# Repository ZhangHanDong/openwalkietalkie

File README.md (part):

# Cohdl OpenWalkieTalkie

[Website and downloads](https://openwalkietalkie.org/) ·
[Latest release](https://github.com/conol-ai/openwalkietalkie/releases/latest)

Firmware and [routed BodyV5 r3 hardware design](hardware/rev-a/README.md) for
OpenWalkieTalkie, a handheld with a touch screen, a scroll wheel, PTT, Enter,
Esc, Shift and two front macro keys. The custom hardware includes a four-layer main PCB and
two-layer encoder PCB, with matching fabrication files and populated 3D models.

The firmware turns the device into the **Agent Command Deck**: a handheld
status board and radio for someone running several AI agent sessions at once.
The screen shows who needs you, PTT talks to the active agent, and the buttons
answer questions and switch channels.

The Rust / [embassy](https://embassy.dev) firmware currently runs on a **LilyGo
T-Display SF32** development board, which carries a SiFli **SF32LB52x** (Cortex-M33,
16MB NOR, 8MB PSRAM) and the same class of 2.16" CO5300 AMOLED with CST9220
touch. The dev board has no scroll wheel, so the **T-SF32-Keyboard** expansion
stands in for the wheel and buttons.

Sibling to [`openmicrokbd`](https://github.com/conol-ai/openmicrokbd) (v1,
STM32F072) — same approach, different silicon.

## What works today

Boot, the debug UART, the shared I2C bus, keypad and touchscreen input,
battery charging, and the Agent Command Deck's 480x480 UI on the AMOLED:
five faces, the face manager, notifications, the PTT LISTENING overlay and a
built-in demo host. Everything above the drivers is covered by host tests and
rendered previews; **none of the deck has been validated on hardware yet**
(see the [first-flash checklist](docs/deck-device-checklist.md)).

The deck is its own USB/BLE HID device: **Cohdl OpenWalkieTalkie**, VID
`0x1209` PID `0x5754`, one vendor collection (usage page `0xFF00`, report id
6, 64-byte reports). Report channel 2 carries a small system RPC
(`sys.version`, `sys.reboot`, `device.status`); the deck faces talk to a deck
host over channel 5 of the same connection ([deck protocol](#the-deck-host)).

The `1209:5754` allocation has been requested in
[pid.codes PR #1312](https://github.com/pidcodes/pidcodes.github.com/pull/1312)
and is pending registry approval. Application firmware and USB recovery use
the same product ID.

Pair **OpenWalkieTalkie** in macOS Bluetooth settings. The latest computer's bond
key and HID/battery notification preferences are stored in an append-only
flash journal at `0x12710000..0x1271FFFF`, reserved from the application
linker region. Automatic encrypted reconnection after a firmware update has
been verified. Upgrading from firmware that kept keys only in RAM requires
forgetting the old device and pairing once to create the persistent bond.

The journal checks each record's version and CRC, skips torn writes, and
verifies writes by reading them back. It supports 1024 changed records and
never erases flash; an exhausted journal reports a storage error. Unchanged
keys/preferences do not consume records. `tools/flash.sh` writes ELF load
segments and preserves the reserved journal. A whole-chip erase does not.
The Embassy target carries controls, deck traffic and battery status over HID.
On Rev A it also carries the microphone and speaker, as its own BLE GATT
service on the same link rather than as a Bluetooth audio device: a PTT press
streams 16 kHz IMA ADPCM to the host, and the host's spoken replies come back
the same way (`docs/deck-protocol.md`, "Voice"). Over the USB cable the same
frames ride report channel 7 of the HID collection, so a deck on the cable
alone has its voice too, with no pairing; `deckd` uses the cable whenever it
is there and Bluetooth otherwise. The
[native audio target](native/README.md) instead presents the display board's
microphone and speaker as Bluetooth Classic audio (HFP/A2DP) alongside the
same UI.
Both targets show the website's pixel-radio icon and stacked OpenWalkieTalkie
title on a black boot splash, with a small COHDL mark and “A COHDL PROJECT”
credit. After 1.2 seconds, the Agents face appears.
The same radio appears in Settings → About and in the Mac app, Dock, menu bar
and updater. Regenerate the desktop assets with `python3 tools/generate-branding.py`
(Pillow); normal builds use the checked-in images.

Embassy boot log, abridged:

```
SFBL
openwalkietalkie-fw 0.1.0
board: LilyGo T-Display SF32 (dev)
board: holding power rail (PA41)
board: bringing up I2C1 (SCL PA38 / SDA PA37) at 400000 Hz
display: CO5300 initialised (480x480, rotation=0deg)
board: display ready
board: ready
boot: OpenWalkieTalkie splash ready
boot: I2C1 before keyboard power-up:
  0x22 XL9555 GPIO expander (keyboard board)
  0x25 AW21009 keypad LED driver (keyboard board)
  0x34 TCA8418 keypad scanner (keyboard board)
app: Agent Command Deck ready
keypad: TCA8418 ready (5x4 matrix), PA11 interrupt + 50ms fallback
```

## Faces

The screen is a strip of faces, one on screen at a time. The default strip,
left to right: **Agents** (the agent-session roster, home), **Omarchy** (a
remote for the Omarchy/Hyprland desktop), **Macropad**, **Usage**, **System**, **Arcade** and
**Settings**.

- **Boot and home are the Agents face.** Until a deck host says hello the deck
  is empty and every face's header tag reads `offline`; a lost host leaves its
  data on screen, gray, tagged `offline`. Settings → Host → Demo data (off by
  default) fills the deck with built-in demo data instead, tagged `demo`, until
  the first real `hello` clears it.
- **SHIFT+SCROLL moves between faces**, one face per detent, clockwise to the
  right, with hard ends and no wrap. On the dev keypad: hold HOME and press ▼
  or ▲.
- **CANCEL at a face's top level goes home.**
- **Double-SHIFT** (two quick taps of HOME, nothing else in between) opens the
  face manager: reorder, add and remove faces (at most eight, three Macropads).
  Agents and Settings stay pinned.
- **PTT talks to an agent from work faces**, over a full-screen LISTENING
  overlay. On Arcade it is a local game button and never opens the microphone.
- **A new question or finished task raises a toast** for 4 seconds; tapping it
  jumps to the card. Unread notices wait in a drawer (swipe down from the top
  edge), flagged by a pill at the top of the screen, red while a question waits.
- **Idle-home:** after 120 seconds without local input the deck returns to the
  Agents roster (Settings → Display; off, 30, 60 or 120 seconds). It waits for
  a PTT session to end.
- **Sleep locks every local control, including PTT.** Any button, wheel detent
  or touch lights the lock screen. Turn the wheel counterclockwise four ticks
  to unlock; clockwise rotation resets progress. The unlocking ticks and any
  press or touch begun while locked never trigger the underlying screen.

[The Agent Command Deck](docs/agent-command-deck.md) is the full grammar: views,
cards, the manager, notifications, settings and the PTT session rules.

### Fonts

Deck text is Noto Sans (SIL Open Font License, `assets/fonts/`), rasterized
ahead of time into 4-bit glyph atlases by `tools/generate-ui-fonts.py`; the
firmware carries no font engine. The panel is small and dense (480 px over
38.8 mm, about 12 px/mm), so the type ramp runs about 1.6x the mockups' sizes:
15 px for hints, 18 px for tags and labels, 22 px body text, 25 px list rows and
up to 48 px for the big numbers (`RAMP` in `tools/generate-ui-fonts.py` and
`src/ui/theme.rs`). The mockups' layout rectangles are kept where the larger
text fits, and moved where it does not (the question card's choices start
lower; the PTT pill is wider). `tools/generate-ui-fonts.py --check`
regenerates into a temporary directory and diffs; the atlases depend on the
local FreeType build, so a check on another machine may differ.

Chinese text falls back to Noto Sans CJK SC: 28,491 glyphs covering simplified
and traditional Chinese, Extension A, Chinese punctuation and fullwidth
forms. A shared 26 px, 2-bit atlas is filtered to each text size, keeping the
firmware inside the board's application partition. The host uses the same
metrics when wrapping messages. Regenerate it with
`python3 tools/generate-cjk-font.py` (or verify with `--check`); source,
license and coverage details are in `assets/fonts/gen/README.md`.

### The deck host

The deck faces are drawn from data a host daemon pushes over HID channel 5:
agents, cards, replies, transcripts, workspaces, macros and usage. The device
sends back keys, answers, PTT edges, channel switches and settings. The wire
contract is [docs/deck-protocol.md](docs/deck-protocol.md). The host is
[`deckd`](host/README.md), the Rust service in `host/`: today it owns the link
(hello, sync barrier, heartbeat, the paced outbox), a demo roster
(`deckd run --demo`) and its open API — JSON-RPC over a Unix socket and over
`127.0.0.1:47201` (HTTP, WebSocket, SSE), so a script or a `curl` one-liner can
be an agent on the deck and answer its own cards; the Claude Code and Codex
hook adapters, voice and the gpui GUI follow the plan in
[docs/host-service.md](docs/host-service.md) (status at its top; research in
[docs/host-research/](docs/host-research/)). `tools/deck-sim.py` remains the
reference host: it runs the mockup session against a device, `--dry-run` prints
the framed reports without hardware, and `tools/host-test.sh` diffs `deckd`'s
framing against it.

The deck's spoken replies are bring-your-own-key: give `deckd` an OpenAI or
ElevenLabs API key (on the app's Voice screen under *Spoken replies*, or
`deckd tts key set --provider openai`, typed without echo or piped in) and
the announcements are synthesised by that provider's model
(`gpt-4o-mini-tts`, `eleven_flash_v2_5`), streamed as it is generated; without
a key, Apple's synthesiser speaks on the Mac and nothing leaves the machine.
The key takes effect at the next announcement, no restart, and a provider that
refuses or a dead network falls back to Apple's voice. Or keep the voice on the
Mac: a Kokoro voice (Chinese and English, 103 speakers, a one-time 365 MB
download that the app offers at first start, or `deckd tts install`) speaks
entirely on the machine. `deckd tts status` says which is speaking. The
Qwen3-TTS sidecar (`[voice.tts] engine = "mlx"`, `deckd tts install --mlx`,
needs `uv`) remains available for its voice quality. Speech
recognition is Apple's on-device recogniser by default, and it too can be a
local model: opt in to Whisper (large-v3-turbo, a one-time 1.6 GB download
that the app offers at first start, or `deckd stt install`) and the deck
recognises Chinese and English in one utterance, still entirely on the Mac.
Nothing is downloaded until you say so.

The Usage face is fed by `deckd` itself, the way Zeron does it: the Claude
account's rate-limit windows come from Anthropic's `/api/oauth/usage` with the
Claude Code login (on macOS the `Claude Code-credentials` Keychain item, which
macOS asks about once — *Always Allow* keeps it quiet; a *Deny* leaves the
Claude bars empty), polled every five minutes, and the Codex account's from the
Codex app-server, which also pushes them after every turn. One bar per window
(`Claude session`, `Claude week`, `Codex session`, …) with the countdown to its
reset; ENTER on the face probes both at once. `[usage] providers` in
`config.toml` picks the providers, and a chained `deckd hook claude-statusline`
is read too when the operator has one.

### System Status

The deck's **System** face shows the connected Mac's CPU load, memory used / total,
GPU load and free / total startup-volume storage. `deckd` samples every two seconds;
the meters refresh only when their displayed values change. CPU load is normalized
across all cores, memory includes app, wired and compressed memory, and storage is
the writable startup data volume. GPU load comes from the graphics driver's IOKit
counters (the busiest accelerator when there is more than one).

Unavailable counters show **Not available**. After ten seconds without a sample,
the retained readings are gray and marked **STALE**; a lost host is **OFFLINE**.
The Mac app has no additional page. System follows Usage in a fresh default strip;
for a saved layout, double-tap Shift → **+** → **System** to add it. Matching
firmware and `deckd` are required; telemetry is not sent to older decks.

### Arcade

Three offline games with original pixel art and synthesized 8-bit music:

Gameplay uses the full 480×480 display with an overlaid score. Control hints
appear when starting or pausing; Enter pauses and Cancel returns to the game list.
Snake's corner walls follow the rounded panel so food always stays visible.

| Game | Controls |
| --- | --- |
| Flappy Bird | Tap PTT to fly; avoid pipes and the top/bottom edges. |
| Snake | Turn the wheel clockwise/right or counter-clockwise/left. Left/Right buttons also turn relative to the snake's heading. |
| Raiden (雷电) | Hold Left/Right to move; the plane fires automatically. Three lives. |

Use the wheel and Enter, or touch a menu row, to choose a game. Enter starts,
pauses, resumes or retries; Cancel returns to the game list. Shift+wheel still
changes faces. Leaving the game, opening an overlay or sleeping pauses it.
Best scores last until the device restarts.

**Arcade → Sound → Enter** cycles **Off → SFX only → Music + SFX** (touch works
too). Off is the default; volume follows the Speaker setting. The three original
music loops and seven effects are synthesized locally, with no recorded audio
assets. Pausing/leaving stops sound, host speech takes priority, and microphone
capture silences game audio. A connected app remembers the sound preference;
without the app it lasts for the current boot (the next boot starts Off).

Each tune has a 48-bar arrangement with an intro, theme, answering melodies,
a quieter middle, build and return: Flappy Bird runs 96 seconds, Snake 115.2
seconds and Raiden 76.8 seconds before repeating. Bass patterns, percussion
fills and pulse tones vary between sections. Pausing or retrying the same game
continues its music position; choosing a different game starts that game's tune.

Arcade is in the new default strip before Settings. For a previously saved
layout, double-tap Shift → **+** → **Arcade** to add it. Use matching firmware and
host builds: the wire vocabulary now includes `arcade` and `arcadesound`.

Silent development checks and previews:

```sh
python3 tools/preview-all.py --board hw-a --out target/arcade-preview arcade arcade-flappy arcade-snake arcade-raiden arcade-paused
cargo run --manifest-path native/core/Cargo.toml --example arcade-audio --locked --offline --target aarch64-apple-darwin --target-dir target/native-core-preview -- target/arcade-audio
```

The second command writes three BGM WAVs and seven SFX WAVs without opening an
audio device. These are review exports; the firmware runs the same synthesizer.

## The screen

**The screen mounting is chosen per board at build time.** The default build is
the upright LilyGo T-Display SF32 development board: no physical rotation. The
custom Rev A hardware mounts the panel upside down: build it with
`--features hw-a` (`OWT_BOARD=hw-a tools/build-native.sh` for the native
target), and the boot splash, UI pixels, partial-update windows and touch
coordinates turn 180° together. The shared switch is `ROTATE_180` in
`src/display/orientation.rs`. Both targets print the rotation in their boot
log, and Settings → About shows the board and rotation, so an image built for
the wrong board is easy to spot. `tools/test-all.sh` runs every test in both
configurations. The host UI preview stays upright. See
[rotation and animation validation](docs/display-performance.md#screen-mounting-and-animation).

`hw-a` is the whole Rev A pin map, not only the rotation (`src/board.rs` has
both tables): the panel's two rails are switched on through PA11 (logic) and
PA10 (4 V) before the CO5300 reset sequence, the touch controller sits on
I2C1 at PA42/PA41 with its reset on PA44 and interrupt on PA43, the six
buttons and the wheel are read from GPIOs (`src/input/gpio.rs`), the
MP34DT05 microphone is a PDM part on PA22/PA23 with its supply switched on
PA28 (both images capture it through PDM1; `src/audio/pdm.rs` here), the
NS4150B speaker amplifier is enabled on PA20 behind the SF32's audio DAC
(`src/audio/speaker.rs`), the USB-C
data pair reaches the SF32's own USB block on PA35/PA36 so `src/link/usb.rs`
serves the deck's HID device over the cable as well as over Bluetooth
(the host prefers the cable: it syncs in well under a second and writes a
report in about 0.7 ms where the BLE link needs about 360 ms; on an
Apple-silicon MacBook the first plug-in raises macOS's "Allow accessory to
connect?" prompt and the device stays unconfigured until it is allowed; see
`docs/deck-protocol.md`), and there
is no keypad and no I2C charger: the r6 board's BQ24073 charges on its own
and firmware cannot see its state, so the battery figure follows the voltage
curve in both directions at the usual 1 %/minute, never shows charging, and
100 means the top of the curve rather than a confirmed termination. The native
image follows the same switch through
`OWT_BOARD=hw-a tools/build-native.sh`, which also builds its C side for
Rev A.

`hw-b` is the **Rev B main board** (`hardware/rev-b`): it implies `hw-a`
and overlays the three pins that moved, which is the whole difference. The
NS4150B's enable is on PA1 (PA20 is unconnected), the CAL test pad TP3 is on
PA0 (parked as a pull-down input; set SiFli's calibration tool's signal pin
to PA00), and the BQ24073's CHG output reaches PA33, so Rev B shows
*charging* while the cell takes current and confirms a full charge the way
the dev board does (the pin going high with a USB host attached and the
cell at the charge voltage; on a charger-only supply the end of the charge
reads as no input and the figure holds). Build it with `--features hw-b`
(`OWT_BOARD=hw-b tools/build-native.sh` for the native image, which defines
`OWT_BOARD_HW_B` on the C side); a `hw-a` image boots on Rev B but its
speaker stays silent. Settings → About names the board, `sys.version`
reports it, and `tools/flash-usb.py` refuses an image built for another
board than the running deck reports (`--any-board` overrides). Rev B's UART
pads are the same three, so the first flash is the same procedure, with
the pogo jig in `hardware/rev-b/jig` instead of wires. The r6 board has no USB-serial bridge: `sftool` talks to UART1 on test
pads TP6 (RX) and TP8 (TX) with TP4 as ground. A DAPLink's UART side works
there with `--compat true`, because its USB CDC bridge drops sftool's 64 KiB
stub frame. A blank board needs the flash table and bootloader at
`0x12000000` before the app: `OWT_BOARD=hw-a OWT_BOOT_IMAGES=1
tools/build-native.sh` builds both from `native/boards/openwalkietalkie/ptab.yaml`
(`build_openwalkietalkie_hcpu/ftab.bin` for `0x12000000` and
`bootloader/output/bootloader.bin` for `0x12010000`), and a chip with no
flash table waits in the boot ROM's UART download monitor, so the first
flash involves no reset timing. Later flashes need none either: the debug
port answers while the firmware runs (after a soft power-off wake the deck
by holding PTT for 2 s first), and `tools/flash-uart.py <port>
write_flash --verify <elf>` clears a stale debug session first, hands the
port to sftool and lets it soft-reset the board into the new image. The
bring-up guide has the full procedure. With the `native/bootloader` image in
the bootloader slot (see below), the application also flashes over the
board's own USB-C port: `tools/flash-usb.py <elf>`.

## Touch, battery and rendering

The CST9220 at `0x5A` uses PA0 for reset and PA1 for its active-low interrupt.
Startup checks the controller identity, then enters normal reporting mode.
Each full 15-byte report from `0xD000` is acknowledged with `0xAB`; the marker
and contact count are checked before using coordinates. The driver
exposes one contact with down, move, up, and cancellation events; touch-controller
firmware is left intact. Interrupts wake input processing immediately, with
50ms idle and 20ms active touch fallback polling. The native driver also
latches falling interrupt edges while rendering or replying to the host.
Read failures, invalid or multi-finger reports,
and 120ms without fresh reports cancel the gesture and release held controls.

**Macropad keystrokes.** A Macropad key can carry a keystroke (`cmd+shift+4`),
set in the deck's own key editor (tap `+ assign`, or SHIFT+CANCEL on the
Macropad) or by the host; `deckd` posts it to the desktop through CoreGraphics
whenever the key is pressed. The deck is deliberately not a USB or Bluetooth
keyboard: the SF32LB52x USB block has one IN endpoint besides the control
endpoint, so a keyboard interface of its own cannot exist, and a keyboard
collection beside the vendor one would make macOS class the deck as a
keyboard that no ordinary program may open (Input Monitoring), `deckd` and the
flash tool included. So the daemon types for it, which needs the
**Accessibility** permission. The first refused key press makes macOS put its
own prompt up and list the process under System Settings → Privacy &
Security → Accessibility; switch it on there and the next press goes through
(the prompt names the *responsible* process, so for a `deckd` started from a
terminal that is the terminal's app). Until then the daemon logs each refused
keystroke, `perm.status` says `accessibility: "denied"`, and `perm.request
{which:"accessibility"}` asks again.

**Battery saving.** After 30 seconds without local input the screen dims; after
2 minutes it enters panel sleep and locks all local controls, including PTT.
Any button, wheel detent or touch lights a lock screen. Four consecutive
counterclockwise wheel ticks unlock it; clockwise rotation or another sleep
resets progress. All four ticks are consumed, and a button or touch begun
while locked must be released before a fresh action can be sent. A new deck
card lights the screen for 15 seconds without unlocking or counting as input.
Held controls keep an unlocked screen awake; a button trapped down while
locked does not prevent the display from dimming and sleeping again. The lit level
follows Settings → Display brightness 1–5 (panel 40/80/130/190/255); dim is 32,
or the lit level if lower. Bluetooth audio, host status, deck messages and
charger servicing continue while dark.

**Power off (Rev A).** The board has no power switch: with a cell fitted it
runs until the firmware stops it. Hold CANCEL for 3 s (a `Power off?` dialog
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
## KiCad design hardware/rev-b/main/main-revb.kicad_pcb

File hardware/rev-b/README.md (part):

# OpenWalkieTalkie Rev B main board (BodyV6.13 case)

Rev B is a re-placed and fully re-routed main board, built from the
BodyV6.13 r6 release
([`../rev-a/pcb-release-bodyv6.13-20260923-r6`](../rev-a/pcb-release-bodyv6.13-20260923-r6/README.md)).
The mounting holes and left side switches are unchanged from r6. The outline is r6's, except the **bottom-right corner was rounded to match the top-left** (see Decisions below).

What moved:
- The MCU group is on the front (B, display) side, in the area the display
  covers.
- The antenna sits in the corner below the scroll wheel.
- The battery connector is a 3-pin MX1.25 for a cell with its own NTC.
- The audio path was placed and routed away from the flash and display buses.

The encoder boards did not change: use r6's `encoder/` or `encoder-wheel/`
board with this one.

Status (2026-10-06):

| Check | Result |
|---|---|
| KiCad 10.0.4 DRC, zones refilled, all severities | **0 violations, 0 unconnected** |
| Audio crosstalk check | **0 errors** (4 warnings, all explained below) |
| Placement check | 0 errors (1 proximity warning) |
| 3D fit against BodyV6.13 | No new interference |
| Netlist diff against r6 | Only the intended changes |

An independent six-part review was run and its findings were fixed or written
down (see [Verification](#verification)). **Before ordering, read
[Known limitations](#known-limitations) and [Firmware](#firmware).**

## Files

| What | Where |
|---|---|
| Editable board (KiCad 10.0.4, the authority) | [`main/main-revb.kicad_pcb`](main/main-revb.kicad_pcb) (+ `.kicad_pro`, and `.kicad_dru` with the custom RF/audio rules) |
| Gerbers / drill / stencil | [`main/gerber/`](main/gerber/), [`main/drill/`](main/drill/), [`main/stencil/`](main/stencil/) |
| JLCPCB order package | [`fab-jlcpcb/`](fab-jlcpcb/ORDER-NOTES.md): Gerber + drill zip, BOM, CPL, orientation check list. **Read ORDER-NOTES first.** |
| Design BOM / KiCad positions | [`main/assembly/bom.csv`](main/assembly/bom.csv), [`main/assembly/positions-kicad-all.csv`](main/assembly/positions-kicad-all.csv) |
| Populated STEP | [`3d/main-revb-populated-bodyv6.13.step`](3d/main-revb-populated-bodyv6.13.step) (BodyV6.13 frame), [`3d/main-revb-populated-native.step`](3d/main-revb-populated-native.step), [`3d/bodyv6.13-revb-fit-assembly.step`](3d/bodyv6.13-revb-fit-assembly.step) (case + board + r6 encoder + display/battery envelopes) |
| 3D models | [`models/`](models/ATTRIBUTION.md) (the board references `${KIPRJMOD}/../models/`) |
| Verification reports | [`verification/`](verification/) |
| How the board was built | [`scripts/`](scripts/README.md) |
| UART first-flash jig (pogo plate for blank boards) | [`jig/`](jig/README.md) |

The aligned STEP uses r6's frame: X = u − 28, Z = 47.5 − v, Y along the board
normal. The F (battery) face is at Y 8.275 and the B face at Y 9.275.

## What changed, request by request

| # | Request | What the board does now |
|---|---|---|
| 1 | Charger I²C to the MCU | **Withdrawn**: the standalone BQ24073 stays. The r6 note "CHG to a GPIO" is done instead. The BQ24073's open-drain CHG goes to **PA33** (U5 pin 67), with R46 100k to IO_3V3, and it still reaches TP1. |
| 2 | MCU group on the display side, away from the battery | U5 is on B at (39.0, 24.5), inside the area the display covers. Also on B, all inside the panel outline: the flash U4 (32.6, 14.2), crystal Y1 (41.55, 31.0), buck inductor L3 and the supply caps. Five 0402 caps are on F, outside the battery reserve (v < 23.7): C23/C27/C28/C31 in a row about 3.5 mm north of U5's body (v 17.55), and C15 (AUDIO_REF) just off its east edge. The display FPC receptacle U3 moved from v 48.2 to v 36.75 so the display cable's U-turn clears the re-centred SW3. Tallest B part under the panel: U4, 2.2 mm, under the folded display flex, where 2.9 mm is allowed (3.3 mm elsewhere behind the panel). |
| 3 | Antenna near the scroll wheel | AE1 (Johanson 2450AT18B100E) is on F at (52.2, 24.6), rot 90, in the corner below the wheel. Its clearance is 42.1 mm² (Johanson asks for 42.25), copper-free on all four layers apart from the feed, and open on two board edges. Feed: U5 pin 53 → C57 15 pF (chip-side series; C52/C53 shunt pads DNP) → 50 Ω coplanar line on B (0.16 mm trace, 0.20 mm gaps over In2 GND, fenced) → via → R40 (S1) / L6 (P1, DNP) / R47 (S2) / C58 (P2, DNP) → AE1. S1/S2 are 0R until a VNA tune. The shunt pads have their own GND vias and plane voids underneath. Pin 53 to AE1 is about 20 mm (≈0.4 dB). |
| 4 | PTT and left/right switches centred on their buttons | SW5 (PTT) moved +5.0 mm to v 35.743, the PTT plate centre. SW3/SW4 (front left/right buttons) moved ∓6.52 mm to u 39.72 / 16.28, the cap-flange centres; r6 had them at the rounded outer ends. SW1/SW2/SW6 were already centred. The visible key-top centre is 0.35 mm from the flange centre; if that is the centre you meant, move SW3/SW4 by ∓0.35 mm. |
| 5 | Audio crosstalk with the flash SPI | **Placement:** the flash leaves U5's north face, and the DAC filter leaves the east face at 90° to it. The amplifier U1 is on F with R4/R5 at its input pins, so AMP_INP/AMP_INN are 1.5 mm long with no vias. Both inner layers are solid GND (r6's In2 carried the flash beside AMP_INN). **Routing:** fast nets keep ≥ 0.5 mm from the analog nets on the same layer and never run under them on an adjacent layer. In1/In2 cover 98–100 % of every audio track. The flash's 100 nF now sits at its own VCC pin instead of feeding through the audio-supply node. **Result** ([`verification/audio-xtalk.md`](verification/audio-xtalk.md)): 0 errors. Estimated coupling into the amplifier from fast nets is 0.01 fF·MΩ, against 307.8 fF·MΩ for r6 (about 90 dB less). |
| 6 | Battery with integrated NTC, MX1.25 3-pin connector | J3 is a **Molex 53261-0371** (PicoBlade/MX1.25, 3 positions, SMT right angle; mates with 51021-0300), in r6's J3 position. **Pin 1 CELL, pin 2 NTC → BQ24073 TS, pin 3 GND.** J4 (wire pads) is gone. The cell needs a **10k 103AT (B ≈ 3435) NTC**; without one, TS floats and charging stops. R44 10k (DNP) can stand in on the bench. |
| 7 | TP_VCC connected to 3V3 | U3 pin 6 (TP_VCC) → R48 0R → IO_3V3, decoupled by C20 at pin 8. Lift R48 to float the pin as on r6. |
| 8 | Charge the 500 mAh cell at 0.5 C (2026-10-10) | R37 (BQ24073 ISET) is **3.6k** (Yageo RC0402FR-073K6L, LCSC C137990) instead of r6's 2.55k: 890 / 3.6k = **247 mA**. The input limit stays USB500 (500 mA), so about 250 mA is left for the system before DPPM throttles charging (150 mA before). Termination is the chip's fixed 10 % of ISET, about 25 mA (0.05 C); the BQ24073 has no ITERM pin. Value-only change: copper, gerbers and the CPL are unchanged; BOM, position file, placement check and the 3D model name were updated. |

Carried over from the r6 notes:
- R4/R5 are now at the NS4150B input pins, so the high-impedance summing
  nodes are 1.5 mm long. Their value stays at r6's 22k: R_in does not set the
  r6 hiss, which was flash read bursts clicking into the summing node (see
  the rev-a README). The speaker level is the same as on r6.
- TOUCH_RESET has a 100k pull-down (R45), so the touch controller stays in
  reset while the MCU is asleep or off.

## Decisions and deviations to know about

- **MCU pin map changes.** Firmware must follow; see the next section.
  - AMP_ENABLE moved from PA20 (pin 25) to **PA01** (pin 50). That corner faces
    the amplifier; from the north face the line had no path out of the
    escape fields.
  - The CAL test pad TP3 moved from PA01 to **PA00** (pin 51, unused on r6).
  - CHG_STATUS is new on **PA33**.
  - PA20 is now unconnected.

  SiFli's production downloader and wired crystal calibration (Impeller) use a
  configurable "Signal Pin" that defaults to PA01: **set it to PA00 (TP3)**, or
  use OTA calibration. CAL's via sits in U5 pin 51's pad (filled and capped,
  see ORDER-NOTES).
- **Inner-layer exceptions.** Signals run on F and B, plus six short runs on
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
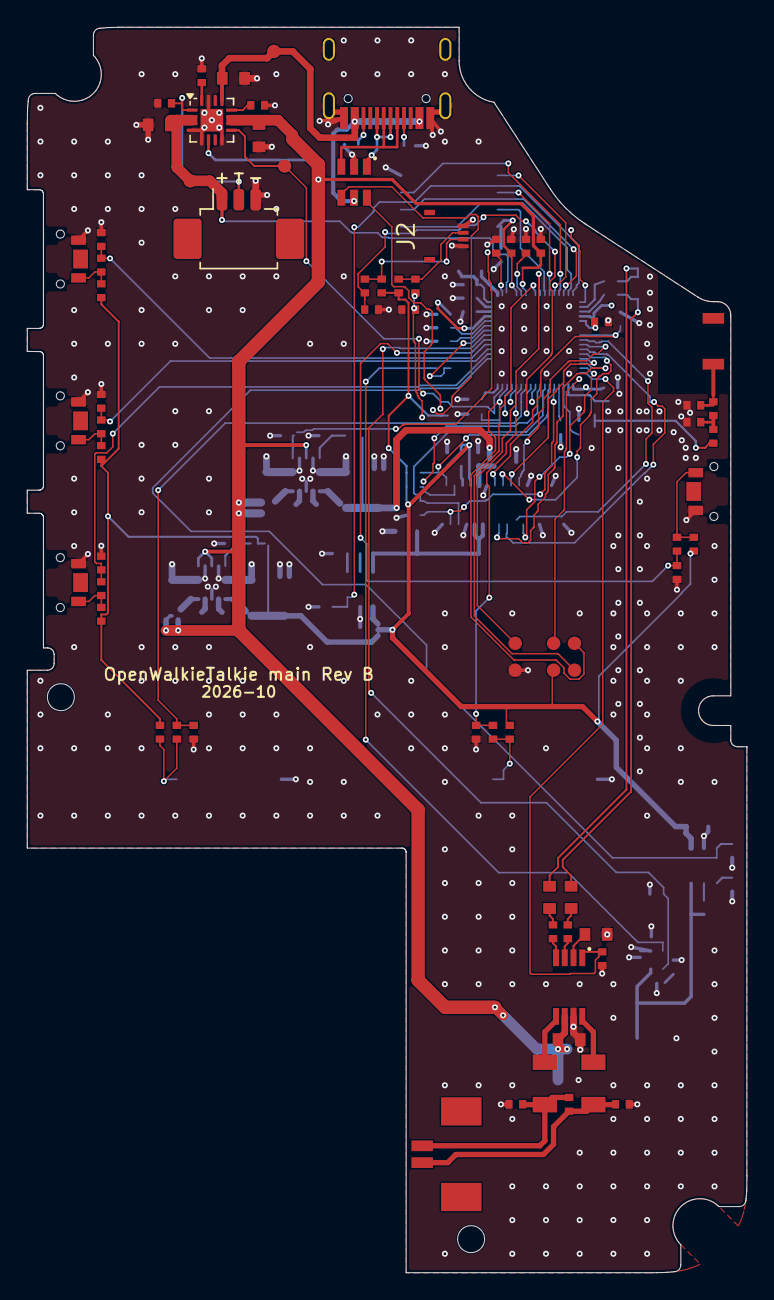
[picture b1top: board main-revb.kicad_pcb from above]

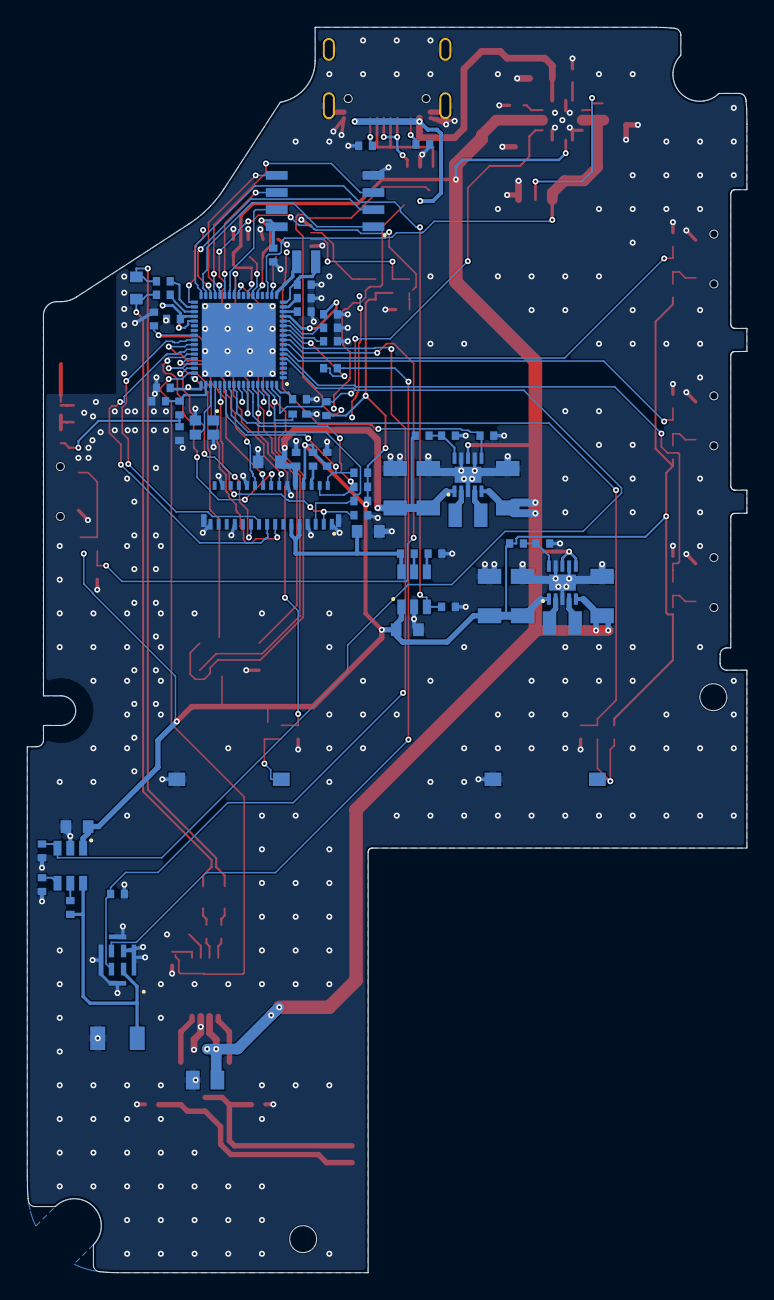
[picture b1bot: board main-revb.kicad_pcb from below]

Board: 4 copper layers, 53.4 x 92.4 mm, 142 parts (67 on the bottom side), 105 nets.

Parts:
AE1: CeramicAntenna2450; antenna-FP_ANT_2450AT18B100E
C1, C3, C4, C5, C11, C21, C49: 1uF; passive-CHIP_0603
C2: 1.5nF; passive-CHIP_0603
C6, C32, C33, C34, C35, C36, C37, C38, C39, C50: 1nF; passive-CHIP_0402
C7: 100nF; passive-CHIP_1206
C8, C9, C10: 330pF; passive-CHIP_0402
C12: 10uF; passive-CHIP_0805
C13, C17, C28, C29, C30: 4.7uF; passive-CHIP_0402
C14, C16, C23, C24, C27, C31: 2.2uF; passive-CHIP_0402
C15, C26: 1uF; passive-CHIP_0402
C18, C40, C41, C48: 4.7uF; passive-CHIP_0603
C19, C20, C22: 100nF; passive-CHIP_0402
C25: 470nF; passive-CHIP_0402
C42, C43, C44, C45, C46, C47: 10uF; passive-CHIP_1206
C52, C53, C58: NF; passive-CHIP_0402
C57: 15pF; passive-CHIP_0402
J1: PicoBlade2Pin; openmicrodial_rev_a-FP_MOLEX_53261_0271
J2: FH34SRJ_4S_0P5SH_99; openmicrodial_rev_a-FP_HIROSE_FH34SRJ_4S
J3: 53261-0371; openmicrodial_rev_b-FP_MOLEX_53261_0371
J5: USB_C_Receptacle_2_0; usb-connectors-type_c-FP_USB_C_Receptacle_HRO_TYPE_C_31_M_12
L1, L2: SpeakerFerrite600R; openmicrodial_rev_a-FP_MURATA_BLM31PG_1P5A_REFLOW
L3: 4.7uH; passive-FP_L_WPN201610U_2016Metric
L4, L5: 2.2uH; passive-FP_L_0806_2016Metric
L6: NF; passive-CHIP_0402
MH2, MH4: Mounting hole; openmicrodial_rev_b-MountingHole_2.0mm_NPTH
MK1: MP34DT05TR-A; openmicrodial_rev_a-FP_ST_MP34DT05_HCLGA_3x4
R1, R2, R8, R20, R21, R22, R23, R24, R25, R26, R27, R35: 1kohm; passive-CHIP_0402
R3, R7, R12, R13, R14, R15, R16, R17, R18, R19, R30, R41, R45, R46: 100kohm; passive-CHIP_0402
R4, R5: 22kohm; passive-CHIP_0402
R6: 22ohm; passive-CHIP_0402
R9, R34, R36, R39, R42: 1Mohm; passive-CHIP_0402
R10, R11: 5.1kohm; passive-CHIP_0402
R28, R29, R44: 10kohm; passive-CHIP_0402
R31: 86.6kohm; passive-CHIP_0402
R32: 604kohm; passive-CHIP_0402
R37: 3.6kohm; passive-CHIP_0402
R38: 3.3kohm; passive-CHIP_0402
R40, R47, R48: 0ohm; passive-CHIP_0402
R43: 180kohm; passive-CHIP_0402
SW1, SW2, SW5, SW6: SKTDLDE010; openmicrodial_rev_a-FP_ALPS_SKTDLDE010
SW3, SW4: TactileSwitchSPST; switches-FP_CK_PTS636SM25
TP1, TP2, TP3, TP4, TP5, TP6, TP7, TP8, TP9, TP10: TestPoint; misc-FP_TEST_POINT_ROUND_1MM
U1: NS4150B; contrib_audio_amp-SOP8P65X490X110N
U2, U10: TPS22918; load_switch-FP_TI_DBV0006A
U3: H0216F002AM; openmicrodial_rev_a-FP_DIANWEI_8_03A5_031250
U4: W25Q128JV; soic-SOIC8P127X790X216N
U5: SF32LB525UC6; openmicrodial_rev_b-FP_SF32LB52X_QFN68L_BSide
U6: BQ24073RGTR; openmicrodial_rev_a-FP_TI_RGT_VQFN16_3x3_EP1p68
U7, U8: RT6150B; qfn-QFN10N50P250X250_1EP120X200
U20: USBLC6; esd-FP_SOT_23_6
Y1: Crystal_4pad; osc-FP_Crystal_SMD_2016_4Pin_E1SB

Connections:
ADC_REF: C13.1, U5.68
AMP_ENABLE: R3.1, U1.1, U5.50
AUDIO_REF: C15.1, U5.39
BT_RF: C52.1, C57.1, U5.53
BUCK_FB: C17.1, L3.2, U5.17
BUCK_LX: L3.1, U5.18
CAL: TP3.1, U5.51
CC1: J5.A5, R10.1
CC2: J5.B5, R11.1
CELL: C40.1, J3.1, TP2.1, U5.20, U6.2, U6.3
DAC_N: R2.1, U5.36
DAC_P: R1.1, U5.37
DEBUG_RX_SWDIO: TP6.1, U5.27
DEBUG_TX_SWCLK: TP8.1, U5.26
ENC_A: C38.1, R26.2, U5.61
ENC_B: C39.1, R27.2, U5.60
ENTER: C33.1, R21.2, U5.8
ESC: C34.1, R22.2, U5.7
FLASH_CLK: U4.6, U5.29
FLASH_CS: U4.1, U5.33
FLASH_IO0: U4.5, U5.30
FLASH_IO1: U4.2, U5.32
FLASH_IO2: U4.3, U5.31
FLASH_IO3: U4.7, U5.28
GND: C1.2, C5.2, C6.2, C7.2, C8.2, C9.2, C11.2, C12.2, C13.2, C14.2, C15.2, C16.2, C17.2, C18.2, C19.2, C20.2, C21.2, C22.2, C23.2, C24.2, C25.2, C26.2, C27.2, C28.2, C29.2, C30.2, C31.2, C32.2, C33.2, C34.2, C35.2, C36.2, C37.2, C38.2, C39.2, C40.2, C41.2, C42.2, C43.2, C44.2, C45.2, C46.2, C47.2, C48.2, C49.2, C50.2, C52.2, C53.2, C58.2, J2.1, J2.4, J3.3, J5.A1, J5.A12, J5.B1, J5.B12, J5.SH1, J5.SH2, J5.SH3, J5.SH4, L6.2, MK1.2, MK1.5, R3.2, R7.2, R9.2, R10.2, R11.2, R30.2, R31.2, R34.2, R36.2, R37.2, R38.2, R39.2, R43.2, R44.2, R45.2, SW1.1, SW2.1, SW3.2, SW4.2, SW5.1, SW6.1, TP4.1, U1.7, U2.2, U3.1, U3.7, U3.12, U3.22, U3.25, U3.28, U3.31, U3.MP, U4.4, U5.69, U6.4, U6.5, U6.8, U6.15, U6.17, U7.3, U7.7, U7.9, U7.11, U8.3, U8.7, U8.9, U8.11, U10.2, U20.2, Y1.2, Y1.4
I2C_SCL: R29.2, U3.5, U5.58
I2C_SDA: R28.2, U3.4, U5.59
IO_3V3: C5.1, C20.1, C43.1, C44.1, C49.1, R12.1, R13.1, R14.1, R15.1, R16.1, R17.1, R18.1, R19.1, R28.1, R29.1, R41.1, R42.1, R46.2, R48.1, TP10.1, U2.1, U3.8, U7.1, U10.1
MACRO_LEFT: C36.1, R24.2, U5.63
MACRO_RIGHT: C37.1, R25.2, U5.62
MCU_LDO1: C14.1, C22.1, C23.1, U4.8, U5.22, U5.38
MCU_LDO2: C24.1, U5.14
MCU_VSYS: C16.1, C31.1, U5.19, U5.52
MIC_PDM_CLK: R6.1, U5.11
MIC_PDM_DATA: MK1.4, R7.1, U5.10
MIC_POWER_ENABLE: R9.1, U2.3, U5.5
PANEL_4V: C18.1, C19.1, C46.1, C47.1, R32.1, U3.10, U8.1
PANEL_CLK: U3.18, U5.47
PANEL_CS: U3.15, U5.48
PANEL_D0: U3.16, U5.46
PANEL_D1: U3.17, U5.45
PANEL_D2: U3.20, U5.44
PANEL_D3: U3.19, U5.43
PANEL_ENABLE: R34.1, U5.35, U8.6
PANEL_LOGIC: C21.1, R35.1, U3.9, U3.11, U10.6
PANEL_RESET: R30.1, U3.14, U5.42
PANEL_TE: U3.21, U5.49
PANEL_VCI_ENABLE: R36.1, U5.34, U10.3
PTT: C32.1, R20.2, U5.9
RESET_ACTIVE_HIGH: R39.1, TP5.1, U5.66
RETENTION: C25.1, U5.13
RTC: C26.1, U5.12
SHIFT: C35.1, R23.2, U5.6
SIP_1V8: C27.1, U5.23
SYSTEM_SUPPLY: C11.1, C12.1, C28.1, C42.1, C45.1, C48.1, TP7.1, U1.6, U5.24, U6.6, U6.10, U6.11, U7.5, U7.6, U7.8, U8.5, U8.8
TOUCH_IRQ: R41.2, U3.2, U5.57
TOUCH_RESET: R45.1, U3.3, U5.56
TP_VCC: R48.2, U3.6
USB_C_N: J5.A7, J5.B7, U20.3
USB_C_P: J5.A6, J5.B6, U20.1
USB_MCU_N: U5.64, U20.4
USB_MCU_P: U5.65, U20.6
USB_VBUS: C41.1, J5.A4, J5.A9, J5.B4, J5.B9, TP9.1, U6.13, U20.5
VOUT1: C29.1, U5.16
VOUT2: C30.1, U5.15
XTAL48_XI: U5.55, Y1.1
XTAL48_XO: U5.54, Y1.3
audio::AC_N: C4.2, R5.1
audio::AC_P: C3.2, R4.1
audio::AMP_BYPASS: C1.1, U1.2
audio::AMP_INN: R5.2, U1.4
audio::AMP_INP: R4.2, U1.3
audio::AMP_VON: L2.1, U1.5
audio::AMP_VOP: L1.1, U1.8
audio::DAC_FILTER_N: C2.2, C4.1, R2.2
audio::DAC_FILTER_P: C2.1, C3.1, R1.2
audio::MIC_CLOCK: MK1.3, R6.2
audio::MIC_DISCHARGE: R8.1, U2.5
audio::MIC_SLEW: C6.1, U2.4
audio::MIC_SUPPLY: C7.1, MK1.1, R8.2, U2.6
audio::SPEAKER_MINUS: C9.1, C10.2, J1.2, L2.2
audio::SPEAKER_PLUS: C8.1, C10.1, J1.1, L1.2
controls::ENC_A_CONTACT: J2.2, R18.2, R26.1
controls::ENC_B_CONTACT: J2.3, R19.2, R27.1
controls::ENTER_CONTACT: R13.2, R21.1, SW1.2
controls::ESC_CONTACT: R14.2, R22.1, SW2.2
controls::MACRO_LEFT_CONTACT: R16.2, R24.1, SW3.1
controls::MACRO_RIGHT_CONTACT: R17.2, R25.1, SW4.1
controls::PTT_CONTACT: R12.2, R20.1, SW5.2
controls::SHIFT_CONTACT: R15.2, R23.1, SW6.2
power::CELL_TEMPERATURE: J3.2, R44.1, U6.1
power::CHG_ILIM: R38.1, U6.12
power::CHG_ISET: R37.1, U6.16
power::CHG_STATUS: R46.1, TP1.1, U5.67, U6.9
power::IO_FB: R42.2, R43.1, U7.10
power::IO_LX1: L4.1, U7.4
power::IO_LX2: L4.2, U7.2
power::PANEL_FB: R31.1, R32.2, U8.10
power::PANEL_LX1: L5.1, U8.4
power::PANEL_LX2: L5.2, U8.2
power::VCI_DISCHARGE: R35.2, U10.5
power::VCI_SLEW: C50.1, U10.4
rf::ANT_MATCH: L6.1, R40.2, R47.1
rf::BT_ANT: AE1.1, C58.1, R47.2
rf::BT_RF_LINE: C53.1, C57.2, R40.1

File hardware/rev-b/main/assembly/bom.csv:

Comment,Designator,Footprint,Manufacturer,MPN,Quantity
2450AT18B100E,AE1,FP_ANT_2450AT18B100E,Johanson Technology,2450AT18B100E,1
1uF,"C1,C3,C4,C5,C11,C21,C49",CHIP_0603,Yageo,CC0603KRX5R6BB105,7
1.5nF,C2,CHIP_0603,Yageo,CC0603JRNPO9BN152,1
1nF,"C6,C32,C33,C34,C35,C36,C37,C38,C39,C50",CHIP_0402,Yageo,CC0402JRNPO9BN102,10
100nF,C7,CHIP_1206,Yageo,CC1206JRNPO8BN104,1
330pF,"C8,C9,C10",CHIP_0402,Yageo,CC0402JRNPO9BN331,3
10uF,C12,CHIP_0805,Yageo,CC0805KRX5R8BB106,1
4.7uF,"C13,C17,C29,C30",CHIP_0402,Samsung Electro-Mechanics,CL05A475MP5NRNC,4
2.2uF,"C14,C16,C23,C24,C27,C31",CHIP_0402,Samsung Electro-Mechanics,CL05A225KP5NSNC,6
1uF,"C15,C26",CHIP_0402,Samsung Electro-Mechanics,CL05A105KA5NQNC,2
4.7uF,"C18,C40,C41,C48",CHIP_0603,Yageo,CC0603KRX5R6BB475,4
100nF,"C19,C20,C22",CHIP_0402,Yageo,CC0402KRX7R7BB104,3
470nF,C25,CHIP_0402,Yageo,CC0402KRX5R6BB474,1
4.7uF,C28,CHIP_0402,Samsung Electro-Mechanics,CL05A475MP5NRNC,1
10uF,"C42,C43,C44,C45,C46,C47",CHIP_1206,TDK,C3216X7R1C106K160AC,6
15pF,C57,CHIP_0402,FH (Guangdong Fenghua),0402CG150J500NT,1
53261-0271,J1,FP_MOLEX_53261_0271,Molex,53261-0271,1
FH34SRJ-4S-0.5SH(99),J2,FP_HIROSE_FH34SRJ_4S,Hirose,FH34SRJ-4S-0.5SH(99),1
53261-0371,J3,FP_MOLEX_53261_0371,Molex,53261-0371,1
TYPE-C-31-M-12,J5,FP_USB_C_Receptacle_HRO_TYPE_C_31_M_12,HRO,TYPE-C-31-M-12,1
SpeakerFerrite600R,"L1,L2",FP_MURATA_BLM31PG_1P5A_REFLOW,Murata,BLM31PG601SN1L,2
4.7uH,L3,FP_L_WPN201610U_2016Metric,Sunlord,WPN201610U4R7MT,1
2.2uH,"L4,L5",FP_L_0806_2016Metric,Murata,DFE201612E-2R2M=P2,2
MP34DT05TR-A,MK1,FP_ST_MP34DT05_HCLGA_3x4,STMicroelectronics,MP34DT05TR-A,1
1kohm,"R1,R2,R8,R20,R21,R22,R23,R24,R25,R26,R27,R35",CHIP_0402,Yageo,RC0402FR-071KL,12
100kohm,"R3,R7,R12,R13,R14,R15,R16,R17,R18,R19,R30,R41",CHIP_0402,Yageo,RC0402FR-07100KL,12
22kohm,"R4,R5",CHIP_0402,Yageo,RC0402FR-0722KL,2
22ohm,R6,CHIP_0402,Yageo,RC0402FR-0722RL,1
1Mohm,"R9,R34,R36,R39,R42",CHIP_0402,Yageo,RC0402FR-071ML,5
5.1kohm,"R10,R11",CHIP_0402,Yageo,RC0402FR-075K1L,2
10kohm,"R28,R29",CHIP_0402,Yageo,RC0402FR-0710KL,2
86.6kohm,R31,CHIP_0402,Yageo,RC0402FR-0786K6L,1
604kohm,R32,CHIP_0402,Yageo,RC0402FR-07604KL,1
3.6kohm,R37,CHIP_0402,Yageo,RC0402FR-073K6L,1
3.3kohm,R38,CHIP_0402,Yageo,RC0402FR-073K3L,1
0ohm,"R40,R47",CHIP_0402,Yageo,RC0402JR-070RL,2
180kohm,R43,CHIP_0402,Yageo,RC0402FR-07180KL,1
100kohm,R45,CHIP_0402,Yageo,RC0402FR-07100KL,1
100kohm,R46,CHIP_0402,Yageo,RC0402FR-07100KL,1
0ohm,R48,CHIP_0402,Yageo,RC0402JR-070RL,1
SKTDLDE010,"SW1,SW2,SW5,SW6",FP_ALPS_SKTDLDE010,Alps Alpine,SKTDLDE010,4
PTS636SM25SMTRLFS,"SW3,SW4",FP_CK_PTS636SM25,C&K,PTS636SM25SMTRLFS,2
NS4150B,U1,SOP8P65X490X110N,Nsiway,NS4150B,1
TPS22918DBVR,"U2,U10",FP_TI_DBV0006A,Texas Instruments,TPS22918DBVR,2
8.03A5.031250,U3,FP_DIANWEI_8_03A5_031250,DIANWEI,8.03A5.031250,1
W25Q128JVSIQ,U4,SOIC8P127X790X216N,Winbond,W25Q128JVSIQ,1
SF32LB525UC6,U5,FP_SF32LB52X_QFN68L_BSide,SiFli Technologies,SF32LB525UC6,1
BQ24073RGTR,U6,FP_TI_RGT_VQFN16_3x3_EP1p68,Texas Instruments,BQ24073RGTR,1
RT6150BGQW,"U7,U8",QFN10N50P250X250_1EP120X200,Richtek,RT6150BGQW,2
USBLC6-2SC6,U20,FP_SOT_23_6,STMicroelectronics,USBLC6-2SC6,1
E1SB48E001G00E,Y1,FP_Crystal_SMD_2016_4Pin_E1SB,Hosonic,E1SB48E001G00E,1

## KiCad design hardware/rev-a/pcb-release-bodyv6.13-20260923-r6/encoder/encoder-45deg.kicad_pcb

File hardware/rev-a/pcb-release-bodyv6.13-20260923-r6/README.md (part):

# OpenMicroDial BodyV6.13 — PCB ECO revision r6

r6 adapts the BodyV6.9 r5 boards to the **BodyV6.13** case (Fusion export
`mechanical-source/case/BodyV6.13.step`). Only the main-board **outline**
changed: footprints, tracks and vias are identical to r5, and the encoder
board is still the r4 board. The main board passes native KiCad 10.0.4 DRC
with zero violations and zero unconnected items, and all fabrication and
assembly outputs below were exported from that file. The review notes for the
r4 re-route (lower-left quadrant) and the r5 part moves (C11/C12/R7) still
apply.

**Updated in place later on 2026-09-23** (still r6, same case): a right-side
screw slot and a cleaner top-left corner were added, see
[r6 update](#r6-update-right-screw-slot-and-top-left-corner). All main-board
fabrication files and 3D models were re-exported after that change. The
encoder board's boss hole MH2 was then enlarged from Ø2.6 to Ø2.8 (see
[encoder holes](#encoder-holes-one-around-the-boss-one-for-the-screw)); it is no longer
identical to r4. Last, the out-of-stock SPM1423HM4H-B microphone was replaced
by the **ST MP34DT05TR-A on the front (B) side**, inside the case's sound post
(see [microphone](#r6-update-microphone-mk1--st-mp34dt05tr-a-on-the-front-side));
the main board's copper around it was re-routed and every main-board output
was exported again. Then the out-of-stock SGM41562SA charger was replaced by
the **TI BQ24073RGTR** (see [charger](#r6-update-charger-u6--ti-bq24073rgtr)),
again with a local re-route and a full re-export. **The battery NTC must now
be 10k and the firmware's SGM41562 driver must go.** On 2026-09-24 the
out-of-stock fixed 3.3 V regulator U7 (RT6150B-33GQW) was replaced by the
adjustable RT6150BGQW (the part U8 already uses) with a feedback divider on the
B side (see [3.3 V regulator](#r6-update-33-v-regulator-u7--rt6150bgqw-with-a-feedback-divider)),
and the main board was re-exported once more. Last, pin-1 dots were added to
the silkscreen next to the ten ICs that had no pin-1 mark (see
[pin-1 dots](#r6-update-pin-1-dots-on-the-silkscreen)); only the two
silkscreen layers changed, and the Gerbers and Gerber zips were rebuilt.
An alternative encoder board with ENC1 on the wheel side, inside a cavity in
the wheel, is in [`encoder-wheel/`](encoder-wheel/README.md) (see
[encoder-wheel variant](#r6-variant-encoder-board-with-enc1-inside-the-wheel)).
It needs a modified wheel.

## Files to use

| Board | Editable KiCad PCB | Fabrication upload | Stencil | Assembly BOM / positions | Populated STEP |
|---|---|---|---|---|---|
| Main, 4 layers (MK1 = MP34DT05TR-A, U6 = BQ24073RGTR, U7 = RT6150BGQW) | [PCB](main/main-45deg.kicad_pcb) | [Gerber + drill ZIP](main/main-gerber-drill.zip) | [paste Gerbers](main/stencil/) | [BOM](main/assembly/bom.csv) / [positions](main/assembly/positions.csv) | [BodyV6.13 aligned](3d/main-populated-bodyv6.13.step) / [native](3d/main-populated-native.step) |
| Encoder, 2 layers (r4 + MH2 Ø2.8) | [PCB](encoder/encoder-45deg.kicad_pcb) | [Gerber + drill ZIP](encoder/encoder-gerber-drill.zip) | [paste Gerbers](encoder/stencil/) | [BOM](encoder/assembly/bom.csv) / [positions](encoder/assembly/positions.csv) | [BodyV6.13 aligned](3d/encoder-populated-bodyv6.13.step) / [native](3d/encoder-populated-native.step) |
| Encoder, wheel-mounted variant (alternative to the row above; ENC1 on the wheel side, needs the [modified wheel](encoder-wheel/mechanical/wheel-with-encoder-cavity-bodyv6.13.step)) | [PCB](encoder-wheel/encoder-wheel-45deg.kicad_pcb) | [Gerber + drill ZIP](encoder-wheel/encoder-wheel-gerber-drill.zip) | [paste Gerbers](encoder-wheel/stencil/) | [BOM](encoder-wheel/assembly/bom.csv) / [positions](encoder-wheel/assembly/positions.csv) | [BodyV6.13 aligned](3d/encoder-wheel-populated-bodyv6.13.step) / [native](3d/encoder-wheel-populated-native.step) |

**Ordering from JLCPCB:** use [`fab-jlcpcb/`](fab-jlcpcb/ORDER-NOTES.md).
It has a Gerber + drill zip per board with paste layers for the stencil, a
BOM with LCSC part numbers and a CPL in JLC's bottom-side rotation
convention. Read `ORDER-NOTES.md` first: Y1 has no LCSC part, and
several lines were out of stock at LCSC on 2026-09-23. The package was
regenerated after the microphone, charger and 3.3 V regulator changes.

Both boards are 1.0 mm nominal. The aligned STEP files are in the
`BodyV6.13.step` frame (X = u − 28, Z = 47.5 − v, board normal along Y,
F/battery side toward −Y), main B face on the pillar seats (Y 8.275–9.275),
encoder B face on the case post shoulder (Y 2.5–3.5).
[bodyv6.13-fit-assembly.step](3d/bodyv6.13-fit-assembly.step) is the V6.13
case (eight solids) plus both populated boards;
`verification/bodyv6.13-fit-model-report.json` is the interference and
clearance report on it.

## What changed in the case (V6.9 → V6.13) and what the board does about it

| Case change (u, v in board mm) | Board response |
|---|---|
| New wall boss on the right side, u 54.0–55.0 × v 49.625–54.375, from the back up through the main-board plane (Y 1–9.28). | The side-button recess on the right edge (edge at u 53.49) now continues straight down to v 54.675 with an r0.5 inner fillet: 0.51 mm to the boss face, 0.30 mm below it. This also removes the old step out to u 54.69 at v 49, so no thin sliver of board is left between recess and notch. No copper was within reach. |
| Left wall rib extended inboard from u 2.0 to u 3.0 (v 47.662–48.662). | Relief extended from u 2.51 to u 3.3 over v 47.342–49.0, r0.5 inner fillets: 0.23 mm minimum. |
| TL and BR pillars joined to the case corner by a diagonal web. | No change needed: the web runs down the existing corner slot with 0.125 mm per side, the same as the pillar clearance. That is tight for a routed edge (fabs typically hold outlines to about ±0.1–0.2 mm) — widen the web gap in CAD or tell me to open the slots if you want more. |
| B-side post at (48, 70.5) hollowed into a ring (outer r4.0 unchanged, bore r3.0). | Nothing to do; C11 / R7 keep 0.43 / 0.54 mm. |
| B-side seat bosses at MH2 (3.8, 51) and MH4 (34.229, 91.2) removed. | Nothing to do; the Ø2.0 holes stay (unused). |
| **Back cover not in the export** (eight solids instead of nine). | Could not be checked: the ENC1-through-cover conflict (15.9 mm³ in V6/V6.9) and the encoder MH2 spigot / cover-boss fit are unverified for V6.13. Export the cover and I will re-run the check. |
| Wheel, side and front buttons, seat block, encoder MH2 spigot | Unchanged. |

Also corrected in r6: the r5 top-edge notch around the seat block was cut on
a wrong assumption about the block's shape (r3.07 about (36.65, 3.6)); the
block is actually r2.875 about the encoder MH1 axis (36.4587, 3.8), so r5's
clearance was 0.159 mm at its tightest, not the 0.24 mm its README claims.
r6 re-cuts that arc concentric with the block: 0.245 mm all round.

## r6 update: right screw slot and top-left corner

| Change (u, v in board mm) | Details |
|---|---|
| **Right screw: open U-slot** into the V6.13 B-side boss at (52.2, 52.0). | 2.2 mm wide, open from the right edge (u 53.49) to a rounded end centred on the boss axis (edges at v 50.9 / 53.1, r1.1 end). The boss has a Ø1.75 blind pilot from its face (Y 9.28) to Y ≈ 12.25, so the screw goes in from the F/battery side through the slot. An F.Cu + B.Cu keepout of r2.5 around the axis keeps tracks, vias, pads, pours and footprints out from under the head and the boss face (nothing was there). Nearest copper is In2.Cu PTT, 1.24 mm from the slot edge; the In1 GND pour is pulled back 0.3 mm. |
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
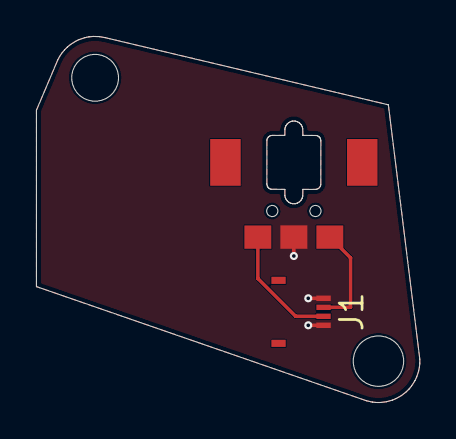
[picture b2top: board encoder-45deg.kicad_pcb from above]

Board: 2 copper layers, 21.3 x 20.3 mm, 4 parts (0 on the bottom side), 3 nets.

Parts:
ENC1: EC05E1220401; openmicrodial_encoder_rev_a-FP_ALPS_EC05E1220401
J1: FH34SRJ-4S-0.5SH(99); openmicrodial_encoder_rev_a-FP_HIROSE_FH34SRJ_4S
MH1, MH2: Mounting hole

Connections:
ENC_A_CONTACT: ENC1.A, J1.2
ENC_B_CONTACT: ENC1.B, J1.3
GND: ENC1.C, J1.1, J1.4

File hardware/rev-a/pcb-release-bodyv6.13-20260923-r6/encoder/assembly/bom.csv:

Comment,Designator,Footprint,Manufacturer,Quantity
EC05E1220401,ENC1,FP_ALPS_EC05E1220401,Alps Alpine,1
FH34SRJ-4S-0.5SH(99),J1,FP_HIROSE_FH34SRJ_4S,Hirose,1

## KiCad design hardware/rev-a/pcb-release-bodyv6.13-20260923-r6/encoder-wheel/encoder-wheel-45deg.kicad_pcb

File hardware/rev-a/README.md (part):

# OpenWalkieTalkie hardware — BodyV5 r3

This directory keeps one current PCB design: the verified **BodyV5 r3**
four-pin inter-board revision, dated 2026-09-17. Superseded schematics, layouts,
manufacturing snapshots and BodyV4 assemblies are no longer part of this tree.

## BodyV6.13 r6 (2026-09-23) — current ECO under review

[pcb-release-bodyv6.13-20260923-r6](pcb-release-bodyv6.13-20260923-r6/README.md)
adapts r5 to the **BodyV6.13** case (`mechanical-source/case/BodyV6.13.step`).
Main-board outline only (copper and parts identical to r5): the right-edge
recess now clears the new wall boss at v 49.6–54.4, the left-rib relief is
deeper, and the seat-block notch is re-cut concentric with the block (r5's
cut left 0.16 mm there, not the 0.24 mm its README states). Main board native
KiCad 10.0.4 DRC 0/0; encoder board identical to r4. The V6.13 export has no
back cover, so cover-related fit checks are open. Updated in place later on
the same day with an open U-slot on the right edge for an M2 screw into the
V6.13 boss at (52.2, 52.0), and with the two sharp tips beside the top-left
pillar slot removed (DRC 0/0 again, all main-board outputs re-exported).
The encoder board's MH2 (the hole around the case spigot) was then enlarged
from Ø2.6 to Ø2.8 mm; MH1 stays Ø2.6 for the M2 screw into the seat block
(encoder DRC 0/0, outputs re-exported). Last, the microphone MK1 (SPM1423HM4H-B,
out of stock at JLCPCB) was replaced by the top-port PDM **ST MP34DT05TR-A**
on the front (B) side inside the case sound post, with a local re-route of the
main board (DRC 0/0; Gerbers, drill, STEP, fit model and the `fab-jlcpcb/`
package regenerated). Datasheet: `mechanical-source/datasheets/mp34dt05-a.pdf`.
Then the charger U6 (SGM41562SA, also out of stock) was replaced by the
standalone **TI BQ24073RGTR** (no I²C; 349 mA charge, 500 mA input limit,
4.4 V system rail), again with a local re-route, DRC 0/0 and a full re-export.
It needs a **10k battery NTC** instead of the 100k one. The firmware's `hw-a`
builds skip the SGM41562 driver: the BQ24073 has no bus, so charging runs on
its own and the charge state is not visible to firmware.
On 2026-09-24 the out-of-stock fixed 3.3 V regulator U7 (RT6150B-33GQW) was
replaced by the adjustable RT6150BGQW that U8 already uses, with a new 1M /
180k feedback divider on the B side (IO_3V3 ≈ 3.28 V); DRC 0/0 and all
main-board outputs re-exported. The same day, silkscreen pin-1 dots were added
next to the ten ICs that had none (U1–U5, U7, U8, U10, U20, Y1); only the
silkscreen layers changed (DRC 0/0, Gerbers and Gerber zips rebuilt).
An alternative encoder board, `encoder-wheel/`, puts the encoder on the wheel
side inside a cavity in the wheel. It needs the modified wheel in
`encoder-wheel/mechanical/`, and the wheel's hex should be about 1.68 across
flats for either board.
The first assembled r6 main board was brought up on 2026-10-03: every rail
measured as designed, and the board was flashed over UART1 on TP6/TP8 (a
DAPLink's UART side, `sftool --compat true`) with the repo-built flash table
and bootloader (`OMD_BOOT_IMAGES=1`) plus the `hw-a` firmware, which boots,
drives the panel rails and advertises over Bluetooth. With the module first
fitted the glass stayed black and the CST9220 touch controller did not answer
on I²C although PANEL_4V and PANEL_LOGIC were present; reseating the 31-pin
FPC fixed both. (`display.TP_VCC` is the module's own 3.3 V touch-supply
output, so leaving it unconnected is correct.) The same day the firmware's
USB HID link was brought up over J5: the Mac enumerates the deck on PA35/PA36
once macOS's accessory prompt is allowed, and `deckd` syncs over the cable
with 0.7 ms report writes; the USB wiring needed no change and the
unconnected MCU VBUS pin did not matter. With the native image the speaker
played the quiet channel checks audibly and the MP34DT05 microphone captured
speech over the voice link through PDM1 (power switched on PA28), but a
full-scale tone at maximum volume with the board on USB and no cell fitted
reset the MCU after about a second: the charger's 500 mA input limit cannot
carry the NS4150B's peak draw, so SYSTEM_SUPPLY drops out. Loud tests need
the cell; a volume ceiling for cell-less operation is open.
Earlier bench tests found speaker hiss at every volume setting. The PSRAM
workaround was removed on 2026-10-17 after the clock correction appeared to
resolve it. Hiss returned in the 2026-10-20 listening test, so Rev A builds
again copy code, constants and fonts to PSRAM and vectors to SRAM at startup.
The corrected clock configuration remains in place.

The original diagnosis excluded the DAC
(measured 2026-10-04/05 with the deck's own microphone through the
`audio-debug` bench RPCs, R4/R5 22 kΩ as released): it is a train of clicks, one per external-flash read burst, coupled
into the amplifier's input summing node. AMP_INN runs on In2.Cu across
FLASH_CLK, FLASH_IO0, FLASH_IO2 and FLASH_IO3, so every execute-in-place
cache fill from the NOR clicks; with the radio busy the Bluetooth host stack
runs at each 15 ms connection event and the clicks form a 66.7 Hz comb that
sounds like hiss. Controlled tests: flash-read bursts at 66 Hz with the radio
quiet reproduce it (−57 dBFS(A) at the mic for 256 lines a burst) while the
same bursts from SRAM or PSRAM, or with the amplifier off, stay at the floor
(−80 to −83); no DAC or codec setting (mute, DAC/AMP/VCM enables, chopper,
low-power and bias modes) and no radio TX power change moved it, and halving
the flash pads' drive strength bought only 3 dB. Because the injection is at
the summing node, its level is set by the NS4150B's 300 kΩ feedback, not by
R_in: changing R4/R5 would not reduce this noise. The workaround first used
on 2026-10-05 runs code from the in-package PSRAM, whose bus never reaches
the PCB. `link-psram.x` places `.text`, `.rodata` and `.flash_assets` in
PSRAM starting at 0x60000000. `src/xip.rs` copies and verifies all three
regions and moves the vector table to SRAM before normal startup. Only
`hw-a` without `hw-b` uses this layout. Font load images still occupy the
upper NOR bank, preserving both Bluetooth stores. The first 7 MiB of PSRAM
must fit the copies and runtime buffers; the last MiB remains diagnostic
scratch. Failed copies retry three times, then reboot into USB recovery.
The original October 5 measurements were: speaker
on, silence streamed over BLE: −60 → −81.9 dBFS(A) (speaker off −82.1); BLE
mic loopback over silence on the shipping image −59 → −81.7; USB RPC traffic
−64…−69 → −79…−81. For the next revision: put R4/R5 at the NS4150B's input
pins so the high-impedance AMP_INP/AMP_INN stubs are millimetres long, and
route the amplifier input pair away from the flash (MPI2) and panel QSPI
lines, with a ground plane between them, never crossing on an adjacent layer.
The board has no power switch and the IO_3V3 regulator's enable is tied to
SYSTEM_SUPPLY, so with a cell on J3 the MCU runs until firmware stops it.
On 2026-10-03 the `hw-a` firmware gained a soft power-off (hold CANCEL 3 s):
it unpowers the panel and enters the SF32LB52x PMU's shutdown state with
PA26 (CANCEL) and PA24 (PTT) armed as the two PMU wake pins through their
RTC-domain PBR pads; IO_3V3, the touch controller, the control pull-ups and
the BQ24073 stay up, and USB still charges the cell. Verified the same day
on the first r6 board (chip revision A3): two off/on cycles, one woken by
CANCEL and one by PTT, each a clean cold boot through the bootloader. Since
2026-10-10 only PA24 (PTT) is armed, and the firmware goes back to sleep
unless PTT is still down 2 s after the application starts
(`pmu::POWER_ON_HOLD_MS`); CANCEL no longer wakes the deck.
The same day the bootloader in the 64 KB slot at 0x12010000 was replaced by
`native/bootloader`, the SDK's second stage plus a USB recovery mode (on J5,
as the application's own "Codex Micro" HID device, so no host prompt) entered
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
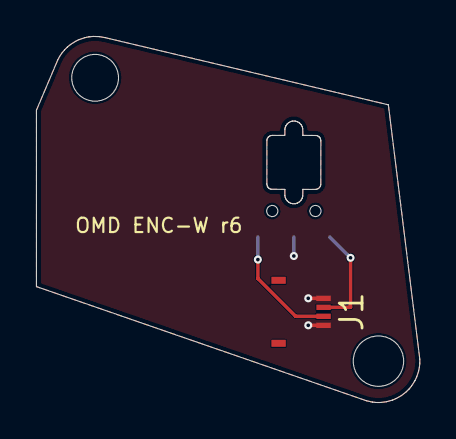
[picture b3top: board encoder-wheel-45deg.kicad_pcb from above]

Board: 2 copper layers, 21.3 x 20.3 mm, 4 parts (1 on the bottom side), 3 nets.

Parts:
ENC1: EC05E1220401; openmicrodial_encoder_rev_a-FP_ALPS_EC05E1220401
J1: FH34SRJ-4S-0.5SH(99); openmicrodial_encoder_rev_a-FP_HIROSE_FH34SRJ_4S
MH1, MH2: Mounting hole

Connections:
ENC_A_CONTACT: ENC1.B, J1.2
ENC_B_CONTACT: ENC1.A, J1.3
GND: ENC1.C, J1.1, J1.4

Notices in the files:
native/src/board.c:
SPDX-License-Identifier: MIT
README.md:
License:
The software is MIT — see [LICENSE](LICENSE). That is everything outside
`hardware/` (firmware, native image, host crates, tools, packaging) plus the
scripts inside `hardware/`, which carry `SPDX-License-Identifier: MIT` headers.
The hardware and mechanical design is CERN-OHL-P-2.0 (the permissive CERN
Open Hardware Licence) — see [hardware/LICENSE](hardware/LICENSE) and
[hardware/README.md](hardware/README.md) for what that covers (CoHDL and KiCad
sources, fabrication outputs, BOMs, case and jig CAD).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
